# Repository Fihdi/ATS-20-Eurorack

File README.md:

# 10hp Radio Module

An ATS-20 Radio port in 3U height. Jumpers on the PCB lets the device be used as an Eurorack module or as a standalone all-band receiver.

A regular 12V DC adapter or a 9V battery can be used for standalone usage.

# Jumpers

Changing the jumper on the back of the module from **SA** (Stand Alone mode) to **ER** (Eurorack mode) changes the output from headphone level to Eurorack level. In stand alone mode, the radio output is routed to an LM386 class AB amplifier. An 8-Ohm speaker can be connected to the amplifier with the **SP+** and **SP-** screw terminals.

The I2C ADDR jumpers change the I2C address of the SI4732 IC.

# 3D Model

The 3D model for the case was designed by [SapuSeven](https://github.com/SapuSeven). The model in this github project is designed for the AS03208AS-HT speaker by PUI audio. The .step model can be downloaded and modified to fit different speakers.

# Sponsorship

The module that you see in the picture above is using circuit boards that were fabricated by [PCBWay](https://www.pcbway.com/) They have excellent build quality and I can recommend using their service to build your own projects! I used the "Black" option for the soldermask and the surface has very deep and glossy black finish, which looks amazing, they also have an option for a "Matte Black" finish which I will try next time. Thank you PCBWay for sponsoring this module. 
This is the first project that features a small OLED display, and thus the first project where I cut out a square section from the frontplate. This worked out really well and the corners are clean 90 degrees with no rounding. They are also having a 3D printing service, which means you can order the boards and the case for this radio all in one place.

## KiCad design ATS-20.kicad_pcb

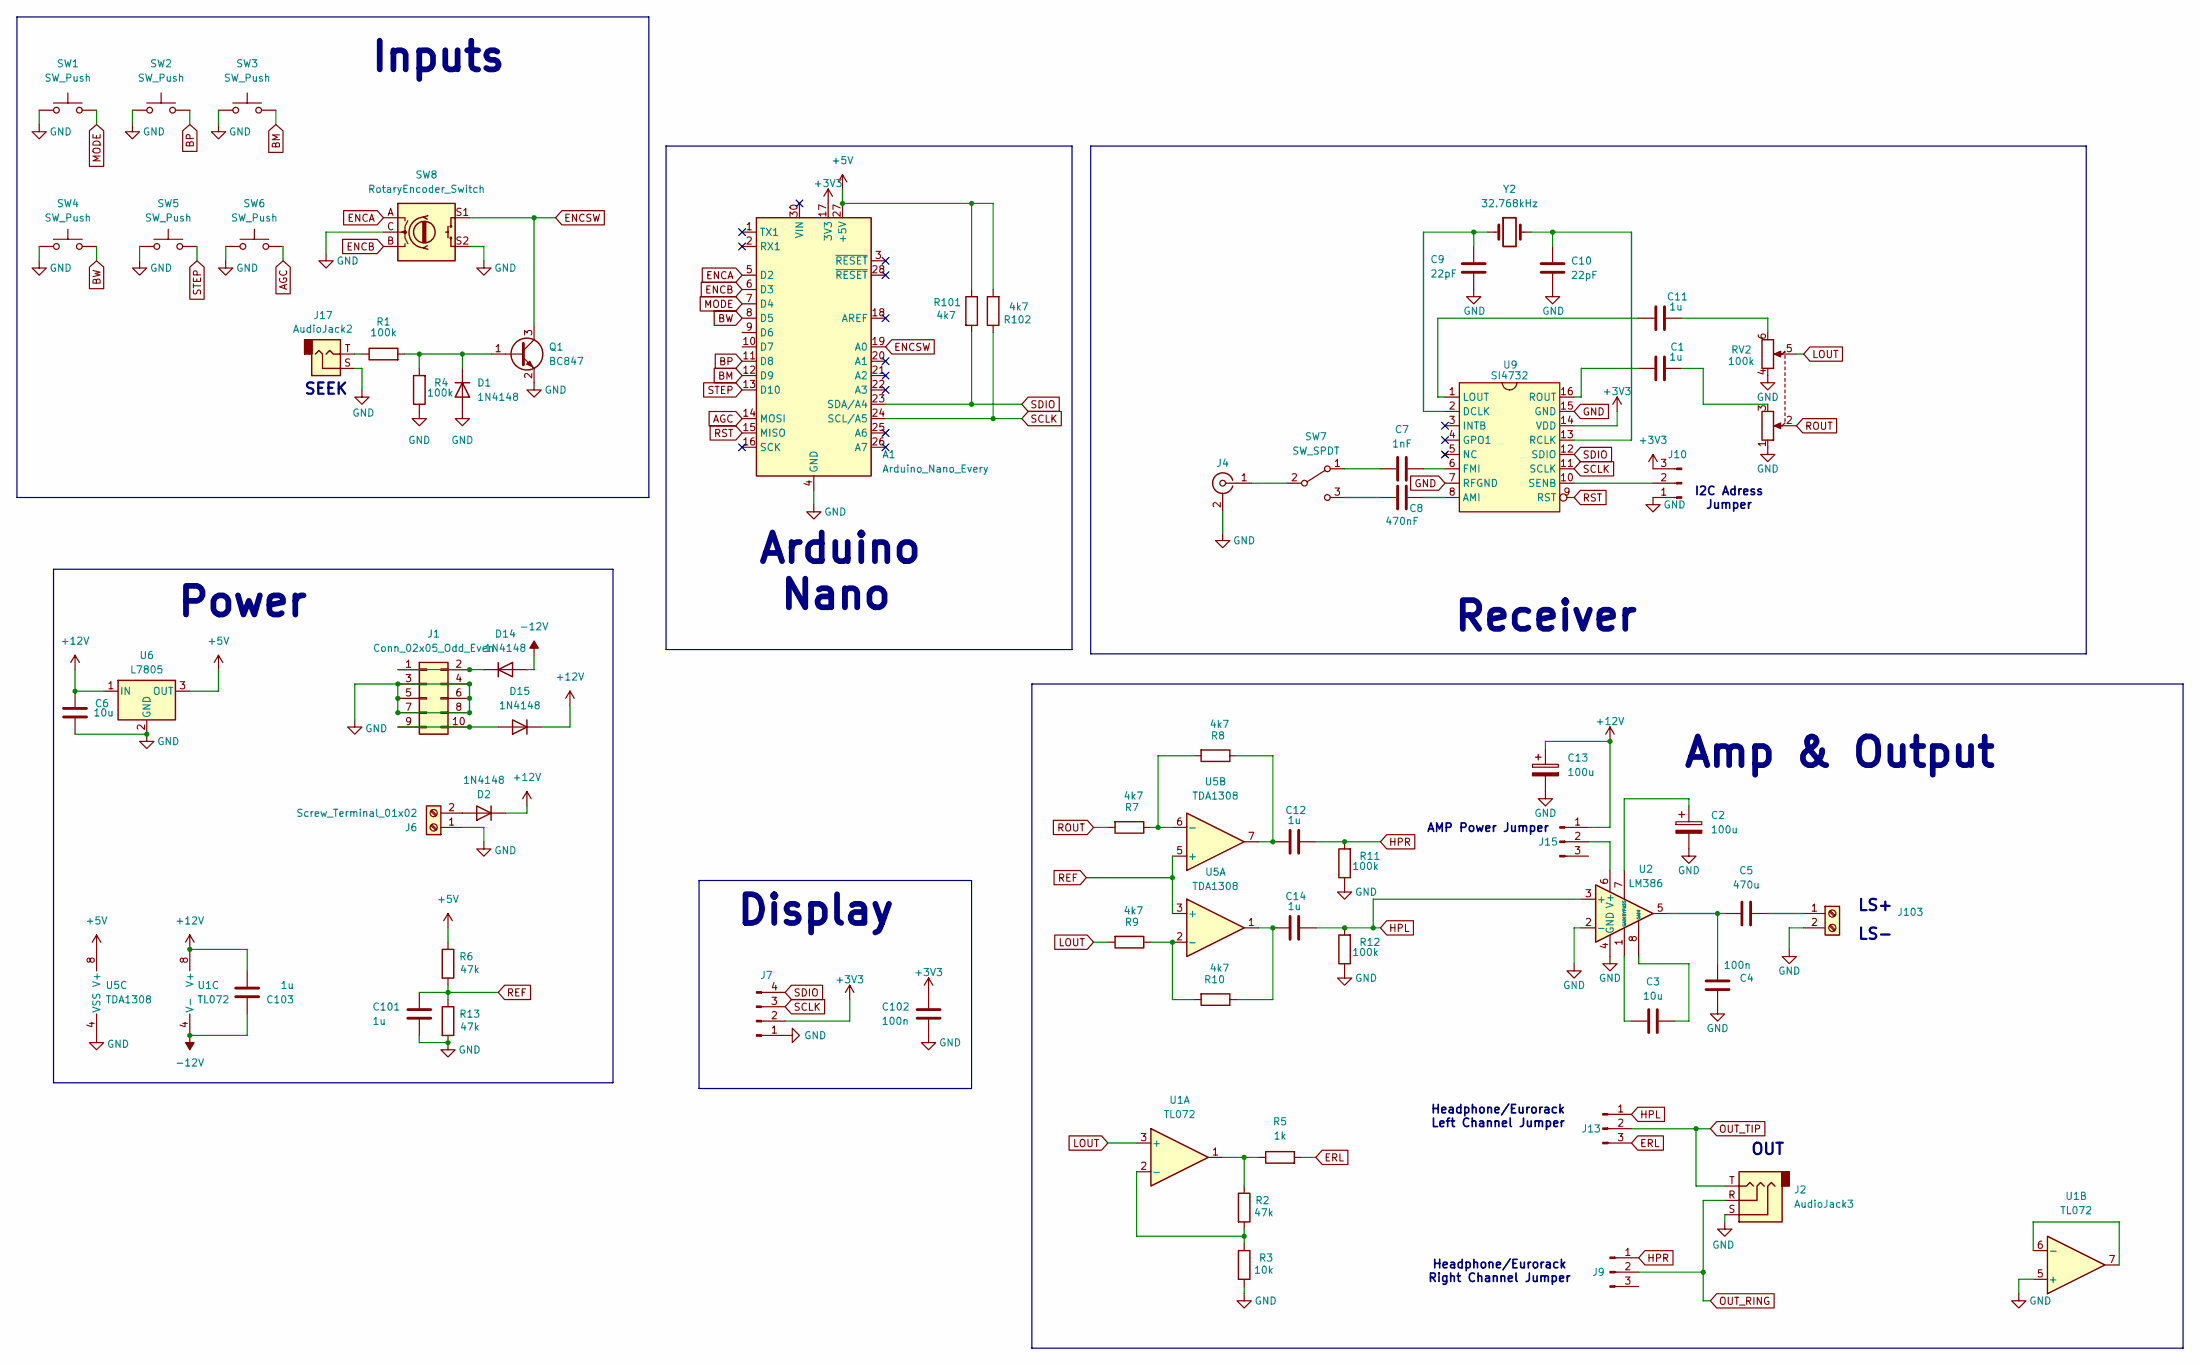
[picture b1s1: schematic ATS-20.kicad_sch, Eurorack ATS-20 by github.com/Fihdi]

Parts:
A1: Arduino_Nano_Every; Arduino_Nano
C1, C11, C12, C14, C101, C103: 1u; C_0805_2012Metric
C2, C13: 100u; C_Elec_6.3x7.7
C3, C6: 10u; C_0805_2012Metric
C4, C102: 100n; C_0805_2012Metric
C5: 470u; C_Elec_6.3x7.7
C7: 1nF; C_0805_2012Metric
C8: 470nF; C_0805_2012Metric
C9, C10: 22pF; C_0805_2012Metric
D1, D2, D14, D15: 1N4148; D_SOD-323_HandSoldering
J1: Conn_02x05_Odd_Even; IDC-Header_2x05_P2.54mm_Vertical
J2: AudioJack3; StereoTRS
J4: Conn_Coaxial; BNC5-J-P-GN-ST-TH2D
J6: Screw_Terminal_01x02; TerminalBlock_Phoenix_MKDS-1,5-2-5.08_1x02_P5.08mm_Horizont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
J7: Conn_01x04_Pin; PinSocket_1x04_P2.54mm_Vertical
J9, J10, J13, J15: Conn_01x02_Pin; PinHeader_1x03_P2.54mm_Vertical
J17: AudioJack2; MonoTRS
J103: Screw_Terminal_01x02; TerminalBlock_RND_205-00287_1x02_P5.08mm_Horizontal
Q1: BC847; SOT-23
R1, R4, R11, R12: 100k; R_0805_2012Metric
R2, R6, R13: 47k; R_0805_2012Metric
R3: 10k; R_0805_2012Metric
R5: 1k; R_0805_2012Metric
R7, R8, R9, R10, R101, R102: 4k7; R_0805_2012Metric
RV2: 100k; Potentiometer_Alpha_RD902F-40-00D_Dual_Vertical
SW1, SW2, SW3, SW4, SW5, SW6: SW_Push; PushButton
SW7: SW_SPDT; Switch
SW8: RotaryEncoder_Switch; RotaryEncoder_Alps_EC11E-Switch_Vertical_H20mm
U1: TL072; SOIC-8_3.9x4.9mm_P1.27mm
U2: LM386; SOIC-8_3.9x4.9mm_P1.27mm
U5: TDA1308; SOIC-8_3.9x4.9mm_P1.27mm
U6: L7805; SOT-223-3_TabPin2
U9: SI4732; SOIC-16_4.55x10.3mm_P1.27mm
Y2: 32.768kHz; Crystal_Round_D3.0mm_Vertical

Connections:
+3V3: A1.17 (3V3), C102.2, J7.2, J10.3, U9.14 (VDD)
+5V: A1.27 (+5V), R6.1, R101.1, R102.2, U5.8 (V+), U6.3 (OUT)
+12V: C6.1, C13.1, C103.1, D2.1 (K), D15.1 (K), J15.1, U1.8 (V+), U6.1 (IN)
-12V: C103.2, D14.2 (A), U1.4 (V-)
AGC: A1.14 (MOSI), SW6.2
BM: A1.12 (D9), SW3.2
BP: A1.11 (D8), SW2.2
BW: A1.8 (D5), SW4.2
ENCA: A1.5 (D2), SW8.A
ENCB: A1.6 (D3), SW8.B
ENCSW: A1.19 (A0), Q1.3 (C), SW8.S1
ERL: J13.3, R5.2
GND: A1.4 (GND), A1.29 (GND), C2.2, C4.1, C6.2, C9.2, C10.2, C13.2, C101.1, C102.1, D1.2 (A), J1.3, J1.4, J1.5, J1.6, J1.7, J1.8, J2.S, J4.2 (Ext), J6.1, J7.1, J10.1, J17.S, J103.2, Q1.2 (E), R3.2, R4.1, R11.1, R12.1, R13.2, RV2.1, RV2.4, SW1.1, SW2.1, SW3.1, SW4.1, SW5.1, SW6.1, SW8.C, SW8.S2, U1.5 (+), U2.2 (-), U2.4 (GND), U5.4 (VSS), U6.2 (GND), U9.7 (RFGND), U9.15 (GND)
HPL: C14.2, J13.1, R12.2, U2.3 (+)
HPR: C12.2, J9.1, R11.2
LOUT: R9.2, RV2.5, U1.3 (+)
MODE: A1.7 (D4), SW1.2
unnamed: C1.2, RV2.3
unnamed: C3.1, U2.8 (GAIN)
unnamed: C3.2, U2.1 (GAIN)
unnamed: C4.2, C5.2, U2.5
unnamed: C11.2, RV2.6
unnamed: C12.1, R8.1, U5.7
unnamed: C14.1, R10.1, U5.1
unnamed: D1.1 (K), Q1.1 (B), R1.2, R4.2
unnamed: D2.2 (A), J6.2
unnamed: D14.1 (K), J1.1, J1.2
unnamed: D15.2 (A), J1.9, J1.10
unnamed: J4.1 (In), SW7.2 (B)
unnamed: J10.2, U9.10 (SENB)
unnamed: J15.2, U2.6 (V+)
unnamed: J17.T, R1.1
unnamed: C5.1, J103.1
unnamed: R2.1, R5.1, U1.1
unnamed: C7.2, SW7.1 (A)
unnamed: C8.2, SW7.3 (C)
unnamed: R2.2, R3.1, U1.2 (-)
unnamed: U1.6 (-), U1.7
unnamed: C2.1, U2.7 (BYPASS)
unnamed: R9.1, R10.2, U5.2 (-)
unnamed: R7.1, R8.2, U5.6 (-)
unnamed: C8.1, U9.8 (AMI)
unnamed: C9.1, U9.2 (DCLK), Y2.1
unnamed: C7.1, U9.6 (FMI)
unnamed: C11.1, U9.1 (LOUT)
unnamed: C10.1, U9.13 (RCLK), Y2.2
unnamed: C1.1, U9.16 (ROUT)
OUT_RING: J2.R, J9.2
OUT_TIP: J2.T, J13.2
REF: C101.2, R6.2, R13.1, U5.3 (+), U5.5 (+)
ROUT: R7.2, RV2.2
RST: A1.15 (MISO), U9.9 (RST)
SCLK: A1.24 (SCL/A5), J7.3, R102.1, U9.11 (SCLK)
SDIO: A1.23 (SDA/A4), J7.4, R101.2, U9.12 (SDIO)
STEP: A1.13 (D10), SW5.2

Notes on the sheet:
SEEK
Power
OUT
Display
I2C Adress Jumper
Amp & Output
Headphone/Eurorack Left Channel Jumper
Headphone/Eurorack Right Channel Jumper
Arduino Nano
LS-
Inputs
Receiver
LS+
AMP Power Jumper

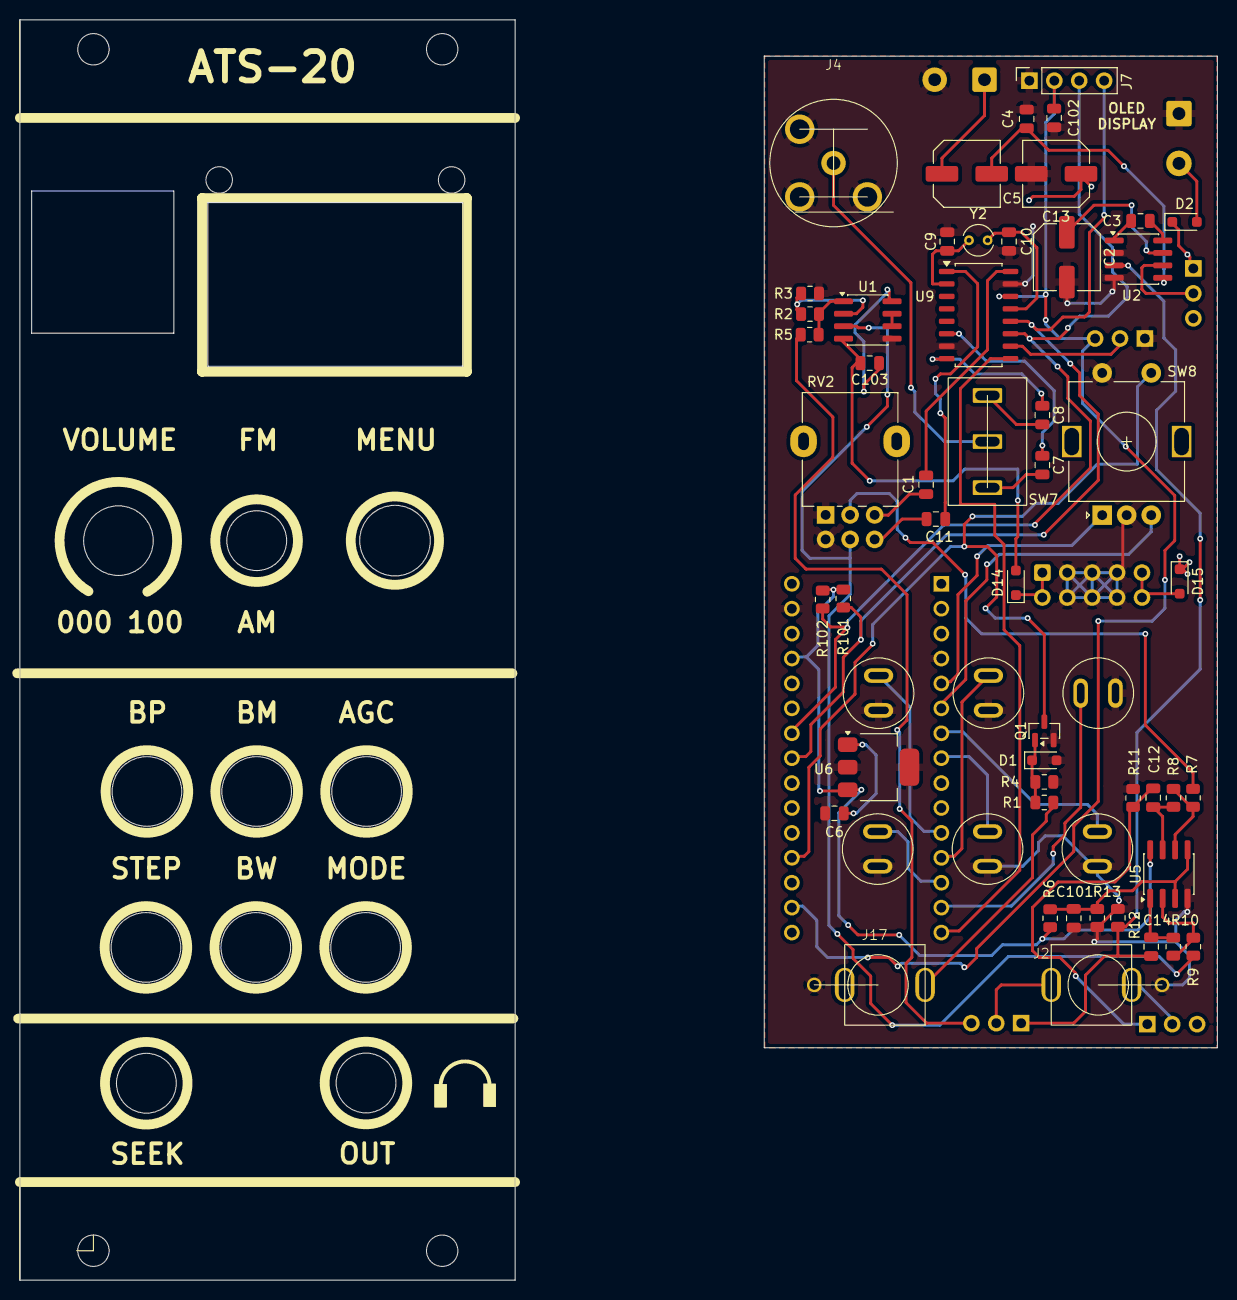
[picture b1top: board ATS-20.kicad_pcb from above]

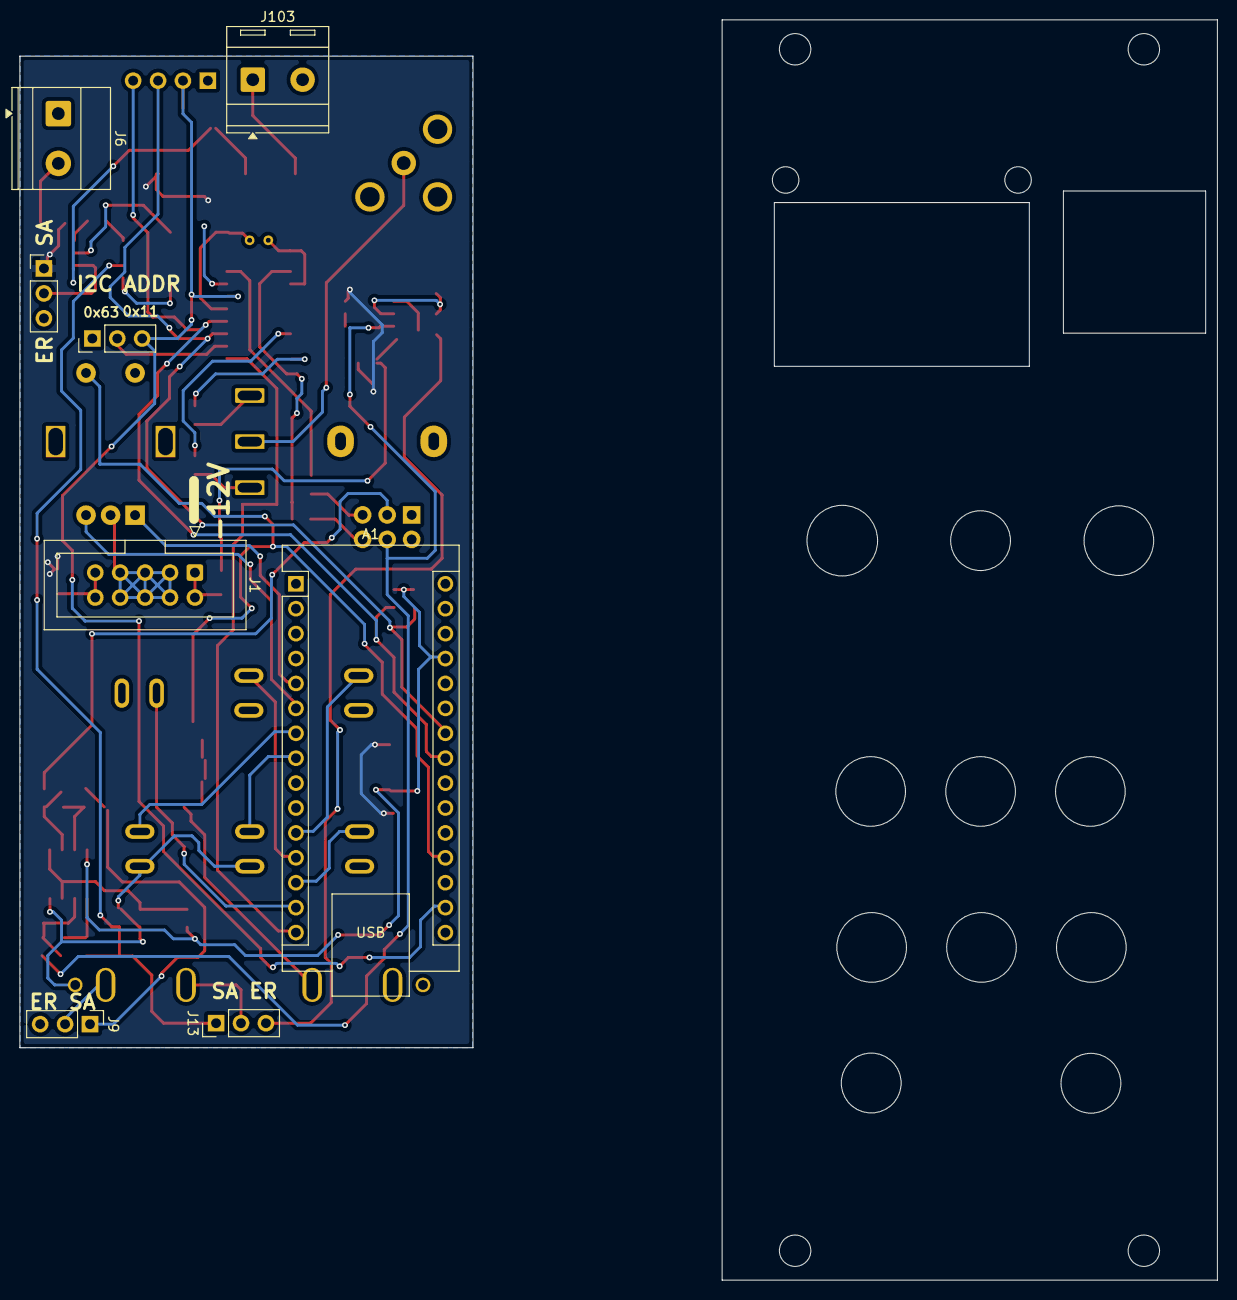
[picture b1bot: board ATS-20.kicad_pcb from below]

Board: 2 copper layers, 46.2 x 101.1 mm, 64 parts (8 on the bottom side), 55 nets.

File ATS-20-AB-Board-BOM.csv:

Reference,Qty,Value,Footprint,Datasheet
A1,1,Arduino_Nano_Every,Module:Arduino_Nano,https://content.arduino.cc/assets/NANOEveryV3.0_sch.pdf
"C1,C11,C12,C14,C101,C103",6,1u,Capacitor_SMD:C_0805_2012Metric,
"C2,C13",2,100u,Capacitor_SMD:C_Elec_6.3x7.7,
"C3,C6",2,10u,Capacitor_SMD:C_0805_2012Metric,
"C4,C102",2,100n,Capacitor_SMD:C_0805_2012Metric,
C5,1,470u,Capacitor_SMD:C_Elec_6.3x7.7,
C7,1,1nF,Capacitor_SMD:C_0805_2012Metric,
C8,1,470nF,Capacitor_SMD:C_0805_2012Metric,
"C9,C10",2,22pF,Capacitor_SMD:C_0805_2012Metric,
"D1,D2,D14,D15",4,1N4148,Diode_SMD:D_SOD-323_HandSoldering,
J1,1,Conn_02x05_Odd_Even,Connector_IDC:IDC-Header_2x05_P2.54mm_Vertical,
J2,1,AudioJack3,Library:StereoTRS,
J4,1,Conn_Coaxial,Library:BNC5-J-P-GN-ST-TH2D,
J6,1,Screw_Terminal_01x02,"TerminalBlock_Phoenix:TerminalBlock_Phoenix_MKDS-1,5-2-5.08_1x02_P5.08mm_Horizontal",
J7,1,Conn_01x04_Pin,Connector_PinSocket_2.54mm:PinSocket_1x04_P2.54mm_Vertical,
"J9,J10,J13,J15",4,Conn_01x02_Pin,Connector_PinHeader_2.54mm:PinHeader_1x03_P2.54mm_Vertical,
J17,1,AudioJack2,Library:MonoTRS,
J103,1,Screw_Terminal_01x02,TerminalBlock_RND:TerminalBlock_RND_205-00287_1x02_P5.08mm_Horizontal,
Q1,1,BC847,Package_TO_SOT_SMD:SOT-23,http://www.infineon.com/dgdl/Infineon-BC847SERIES_BC848SERIE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
"R1,R4,R11,R12",4,100k,Resistor_SMD:R_0805_2012Metric,
"R2,R6,R13",3,47k,Resistor_SMD:R_0805_2012Metric,
R3,1,10k,Resistor_SMD:R_0805_2012Metric,
R5,1,1k,Resistor_SMD:R_0805_2012Metric,
"R7,R8,R9,R10,R101,R102",6,4k7,Resistor_SMD:R_0805_2012Metric,
RV2,1,100k,Potentiometer_THT:Potentiometer_Alpha_RD902F-40-00D_Dual_Vertical,
"SW1,SW2,SW3,SW4,SW5,SW6",6,SW_Push,Library:PushButton,
SW7,1,SW_SPDT,Library:Switch,
SW8,1,RotaryEncoder_Switch,Rotary_Encoder:RotaryEncoder_Alps_EC11E-Switch_Vertical_H20mm,
U1,1,TL072,Package_SO:SOIC-8_3.9x4.9mm_P1.27mm,http://www.ti.com/lit/ds/symlink/tl071.pdf
U2,1,LM386,Package_SO:SOIC-8_3.9x4.9mm_P1.27mm,http://www.ti.com/lit/ds/symlink/lm386.pdf
U5,1,TDA1308,Package_SO:SOIC-8_3.9x4.9mm_P1.27mm,https://www.nxp.com/docs/en/data-sheet/TDA1308.pdf
U6,1,L7805,Package_TO_SOT_SMD:SOT-223-3_TabPin2,http://www.st.com/content/ccc/resource/technical/document/da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
U9,1,SI4732,Package_SO:SOIC-16_4.55x10.3mm_P1.27mm,
Y2,1,32.768k,Crystal:Crystal_Round_D3.0mm_Vertical,

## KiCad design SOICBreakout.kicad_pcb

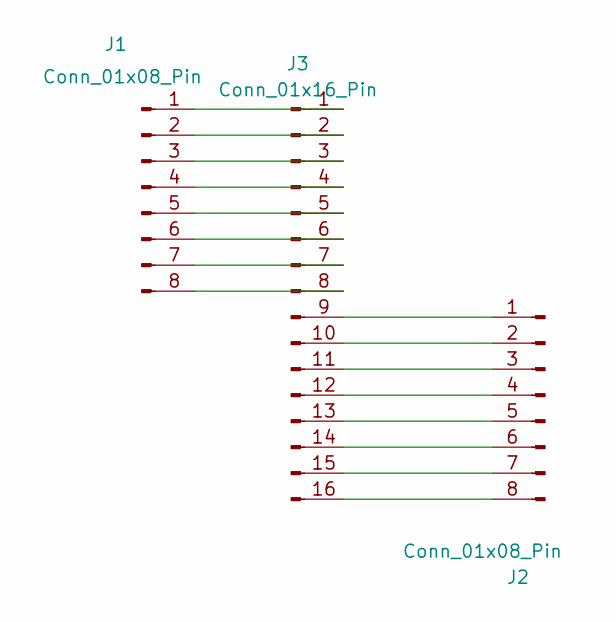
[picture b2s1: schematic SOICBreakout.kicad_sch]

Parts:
J1, J2: Conn_01x08_Pin; PinHeader_1x08_P2.54mm_Vertical
J3: Conn_01x16_Pin; SOIC-16_4.55x10.3mm_P1.27mm

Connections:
unnamed: J1.1, J3.1
unnamed: J1.2, J3.2
unnamed: J1.3, J3.3
unnamed: J1.4, J3.4
unnamed: J1.5, J3.5
unnamed: J1.6, J3.6
unnamed: J1.7, J3.7
unnamed: J1.8, J3.8
unnamed: J2.1, J3.9
unnamed: J2.2, J3.10
unnamed: J2.3, J3.11
unnamed: J2.4, J3.12
unnamed: J2.5, J3.13
unnamed: J2.6, J3.14
unnamed: J2.7, J3.15
unnamed: J2.8, J3.16

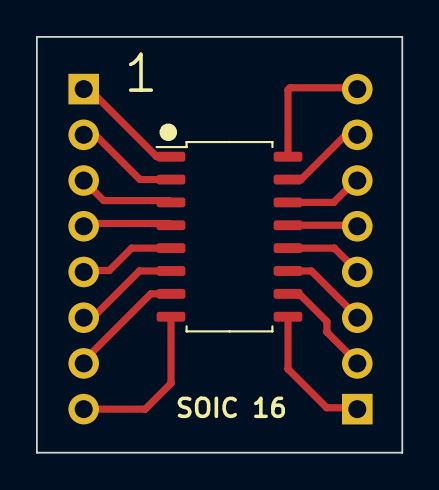
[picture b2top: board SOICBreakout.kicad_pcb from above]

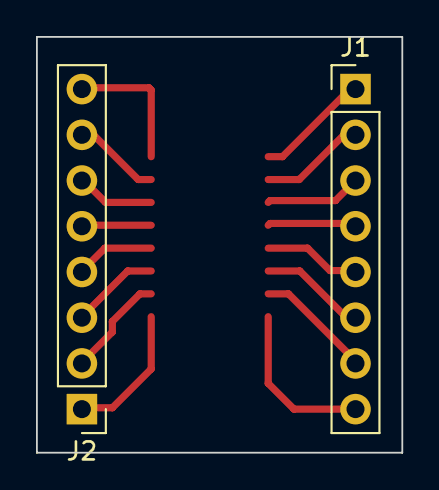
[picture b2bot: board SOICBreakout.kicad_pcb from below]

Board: 2 copper layers, 20.3 x 23.1 mm, 3 parts (2 on the bottom side), 16 nets.

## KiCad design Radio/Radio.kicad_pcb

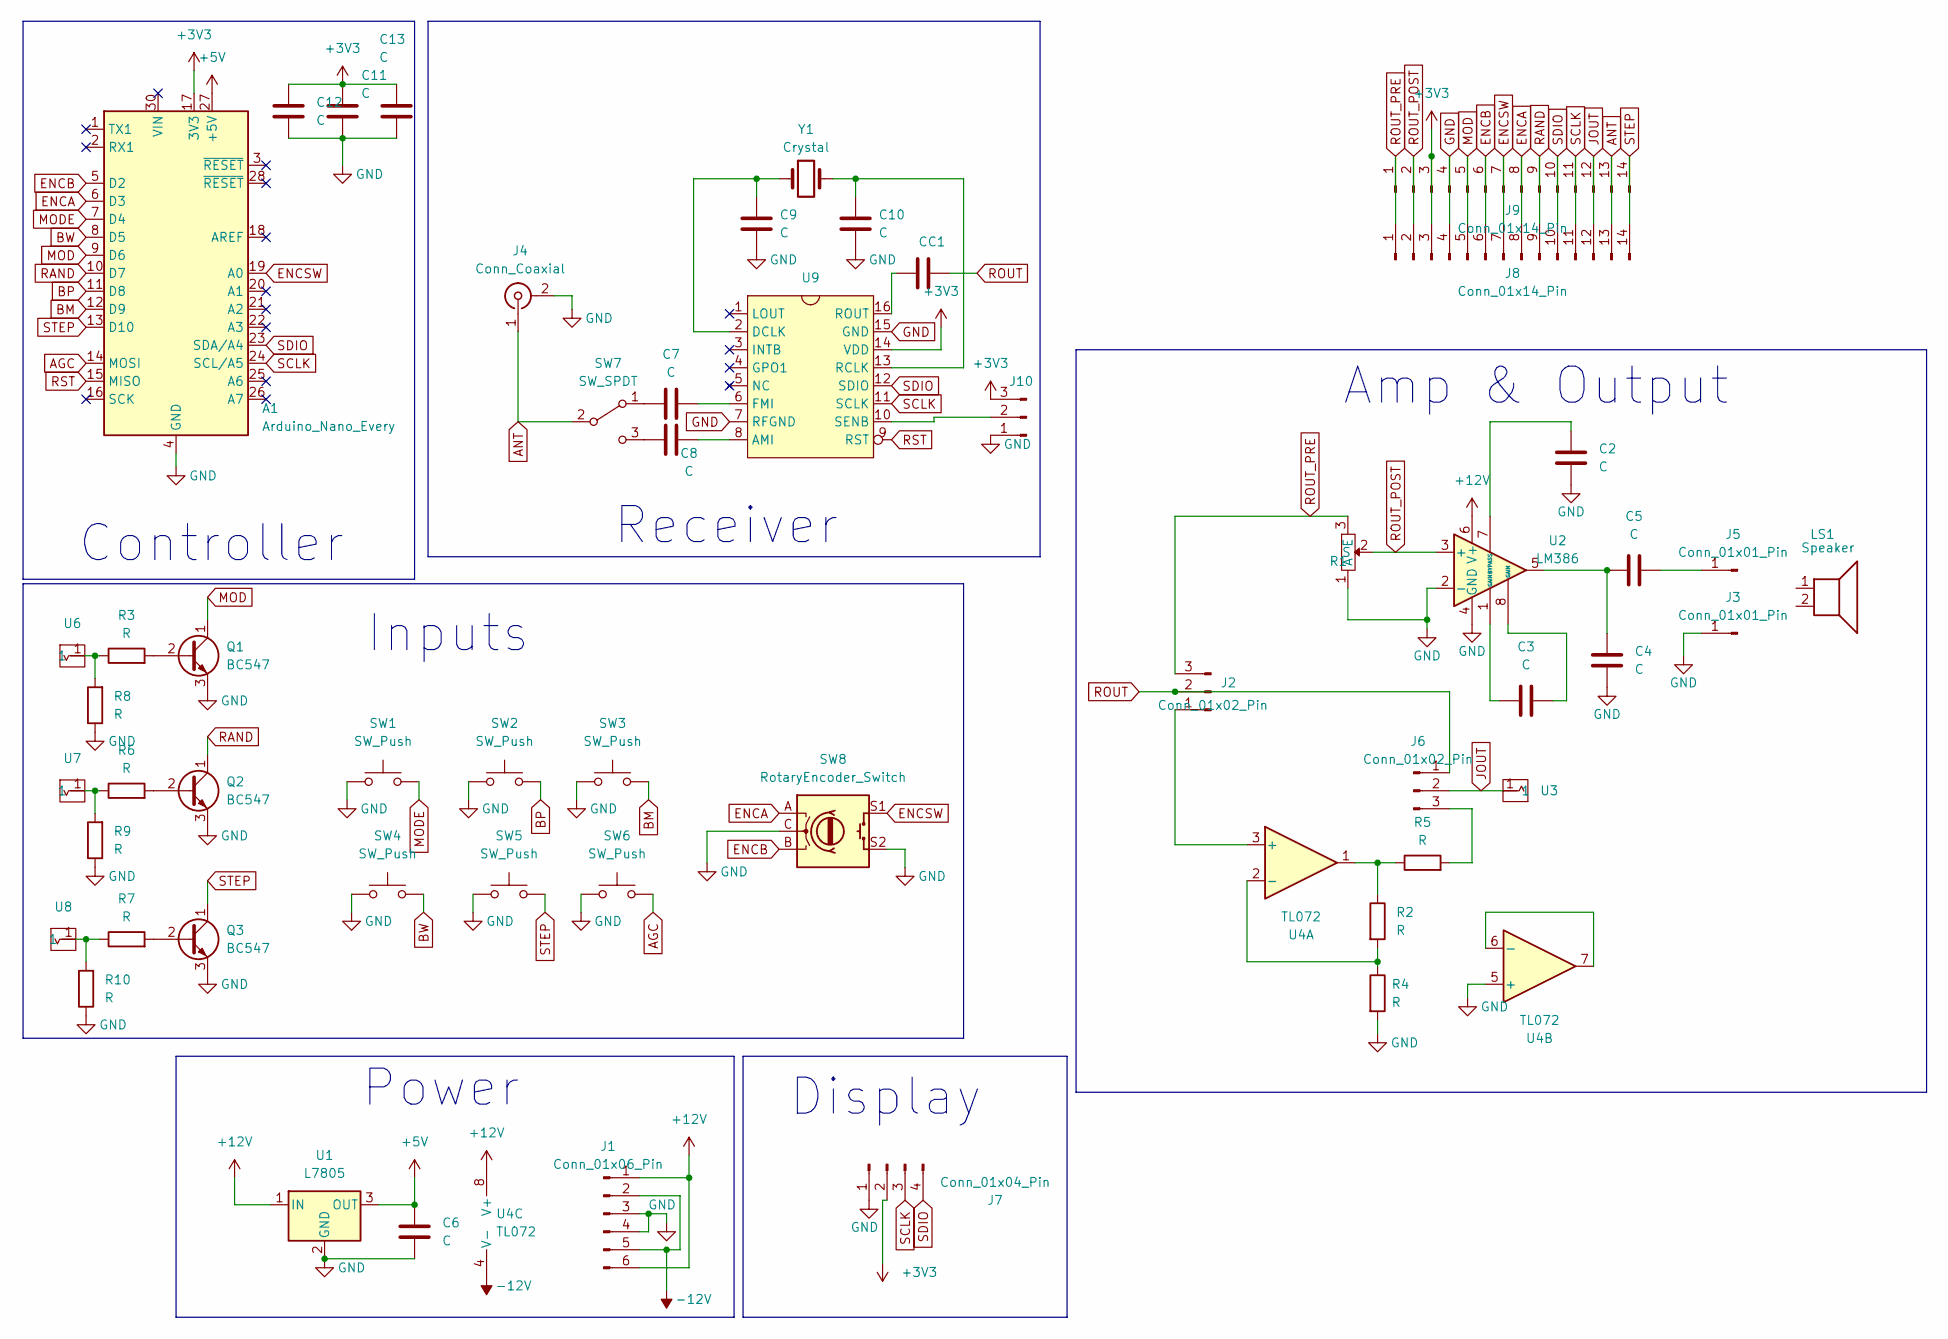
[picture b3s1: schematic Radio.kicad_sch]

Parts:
A1: Arduino_Nano_Every; Arduino_Nano
C1, C2, C3, C4, C5, C6, C7, C8, C9, C10, C11, C12: C; C_Rect_L9.0mm_W2.5mm_P7.50mm_MKT
C13: C; C_Rect_L7.2mm_W2.5mm_P5.00mm_FKS2_FKP2_MKS2_MKP2
J1: Conn_01x06_Pin; PinHeader_1x06_P2.54mm_Vertical
J2, J6, J10: Conn_01x02_Pin; PinHeader_1x03_P2.54mm_Vertical
J3, J5: Conn_01x01_Pin; PinSocket_1x01_P2.54mm_Vertical
J4: Conn_Coaxial; BNC_TEConnectivity_1478035_Horizontal
J7: Conn_01x04_Pin; PinSocket_1x04_P2.54mm_Vertical
J8: Conn_01x14_Pin; PinHeader_1x14_P2.54mm_Vertical
J9: Conn_01x14_Pin; PinSocket_1x14_P2.54mm_Vertical
LS1: Speaker
Q1, Q2, Q3: BC547; TO-92_Inline_Wide
R1: AlpsPot
R2, R3, R4, R5, R6, R7, R8, R9, R10: R; R_Axial_DIN0204_L3.6mm_D1.6mm_P7.62mm_Horizontal
SW1, SW2, SW3, SW4, SW5, SW6: SW_Push; PinSocket_1x02_P2.54mm_Vertical
SW7: SW_SPDT; PinHeader_1x03_P2.54mm_Vertical
SW8: RotaryEncoder_Switch; RotaryEncoder_Alps_EC11E-Switch_Vertical_H20mm
U1: L7805; TO-220-3_Vertical
U2: LM386; DIP-8_W7.62mm
U3, U6, U7, U8: Aux_flush; aux_flush
U4: TL072; DIP-8_W7.62mm
U9: SOIC-16_4.55x10.3mm_P1.27mm
Y1: Crystal; Crystal_DS26_D2.0mm_L6.0mm_Vertical

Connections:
+3V3: A1.17 (3V3), C11.1, C12.1, C13.1, J7.2, J8.3, J9.3, J10.3, U9.14 (VDD)
+5V: A1.27 (+5V), C6.1, U1.3 (OUT)
+12V: J1.1, J1.6, U1.1 (IN), U2.6 (V+), U4.8 (V+)
-12V: J1.2, J1.5, U4.4 (V-)
AGC: A1.14 (MOSI), SW6.2
ANT: J4.1 (In), J8.13, J9.13, SW7.2 (B)
BM: A1.12 (D9), SW3.2
BP: A1.11 (D8), SW2.2
BW: A1.8 (D5), SW4.2
ENCA: A1.6 (D3), J8.8, J9.8, SW8.A
ENCB: A1.5 (D2), J8.6, J9.6, SW8.B
ENCSW: A1.19 (A0), J8.7, J9.7, SW8.S1
GND: A1.4 (GND), A1.29 (GND), C2.1, C4.1, C6.2, C9.2, C10.2, C11.2, C12.2, C13.2, J1.3, J1.4, J3.1, J4.2 (Ext), J7.1, J8.4, J9.4, J10.1, Q1.3 (E), Q2.3 (E), Q3.3 (E), R1.1 (A), R4.2, R8.1, R9.1, R10.1, SW1.1, SW2.1, SW3.1, SW4.1, SW5.1, SW6.1, SW8.C, SW8.S2, U1.2 (GND), U2.2 (-), U2.4 (GND), U4.5 (+), U9.7 (RFGND), U9.15 (GND)
JOUT: J6.2, J8.12, J9.12, U3.1
MOD: A1.9 (D6), J8.5, J9.5, Q1.1 (C)
MODE: A1.7 (D4), SW1.2
unnamed: C3.1, U2.8 (GAIN)
unnamed: C3.2, U2.1 (GAIN)
unnamed: C4.2, C5.2, U2.5
unnamed: J2.1, U4.3 (+)
unnamed: C5.1, J5.1
unnamed: J6.3, R5.2
unnamed: J10.2, U9.10 (SENB)
unnamed: Q1.2 (B), R3.2
unnamed: Q2.2 (B), R6.2
unnamed: Q3.2 (B), R7.2
unnamed: R2.1, R5.1, U4.1
unnamed: R3.1, R8.2, U6.1
unnamed: R6.1, R9.2, U7.1
unnamed: R7.1, R10.2, U8.1
unnamed: C7.2, SW7.1 (A)
unnamed: C8.2, SW7.3 (C)
unnamed: C2.2, U2.7 (BYPASS)
unnamed: R2.2, R4.1, U4.2 (-)
unnamed: U4.6 (-), U4.7
unnamed: C8.1, U9.8 (AMI)
unnamed: C9.1, U9.2 (DCLK), Y1.1
unnamed: C7.1, U9.6 (FMI)
unnamed: C10.1, U9.13 (RCLK), Y1.2
unnamed: C1.1, U9.16 (ROUT)
RAND: A1.10 (D7), J8.9, J9.9, Q2.1 (C)
ROUT: C1.2, J2.2, J6.1
ROUT_POST: J8.2, J9.2, R1.2 (S), U2.3 (+)
ROUT_PRE: J2.3, J8.1, J9.1, R1.3 (E)
RST: A1.15 (MISO), U9.9 (RST)
SCLK: A1.24 (SCL/A5), J7.3, J8.11, J9.11, U9.11 (SCLK)
SDIO: A1.23 (SDA/A4), J7.4, J8.10, J9.10, U9.12 (SDIO)
STEP: A1.13 (D10), J8.14, J9.14, Q3.1 (C), SW5.2

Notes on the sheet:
Amp & Output
Controller
Power
Display
Inputs
Receiver

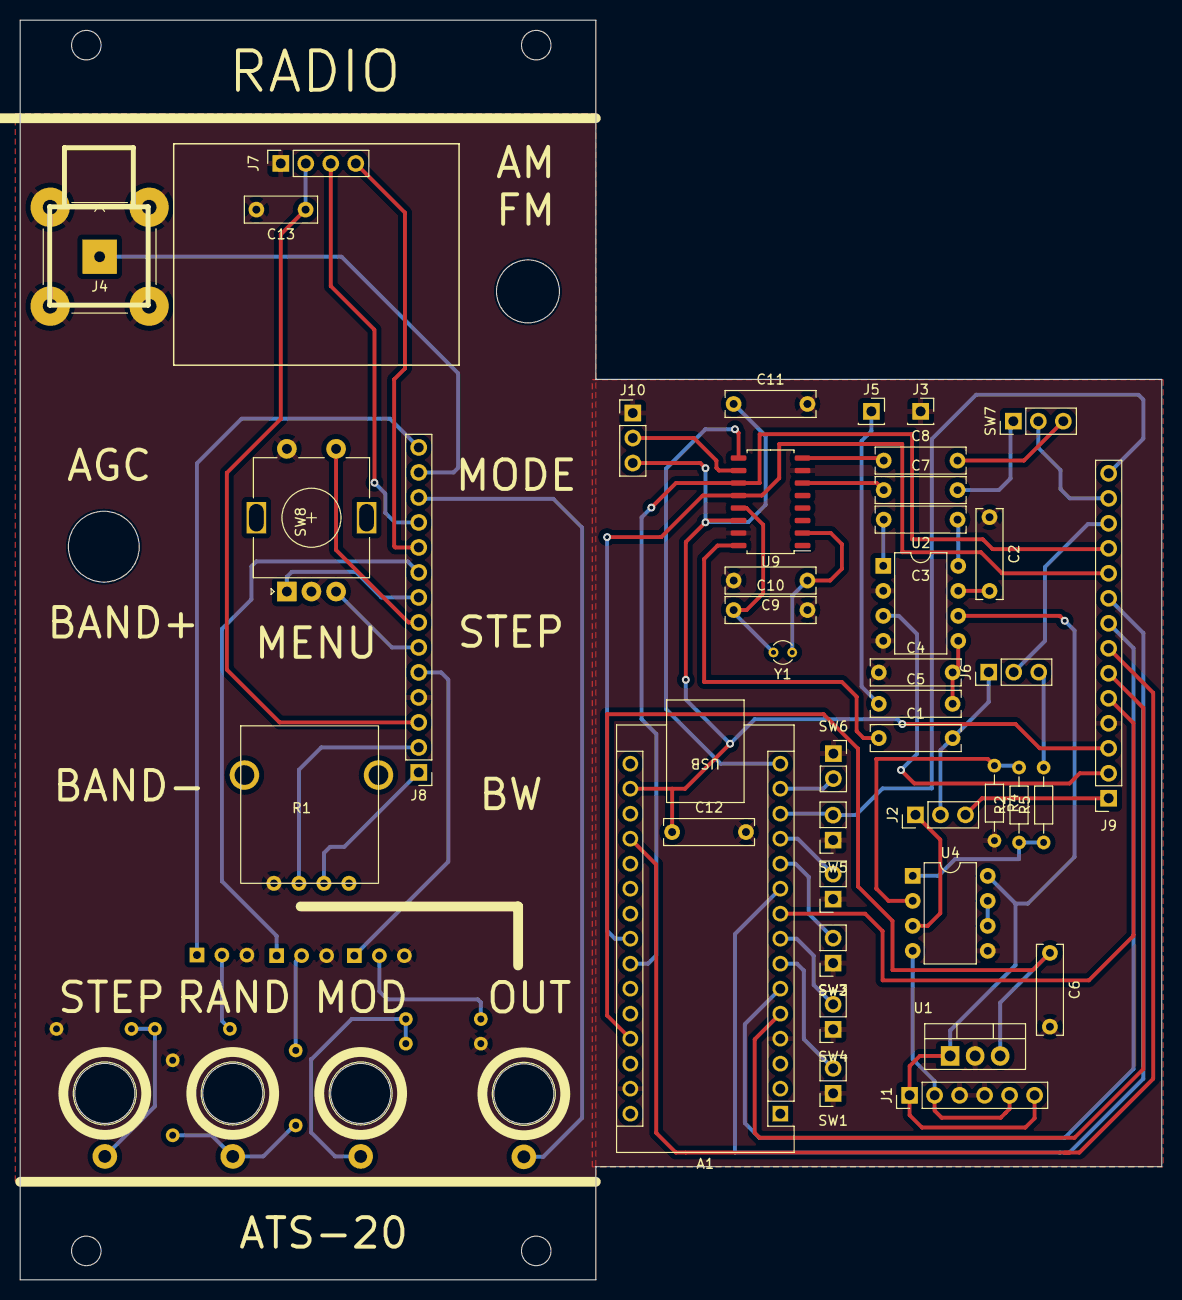
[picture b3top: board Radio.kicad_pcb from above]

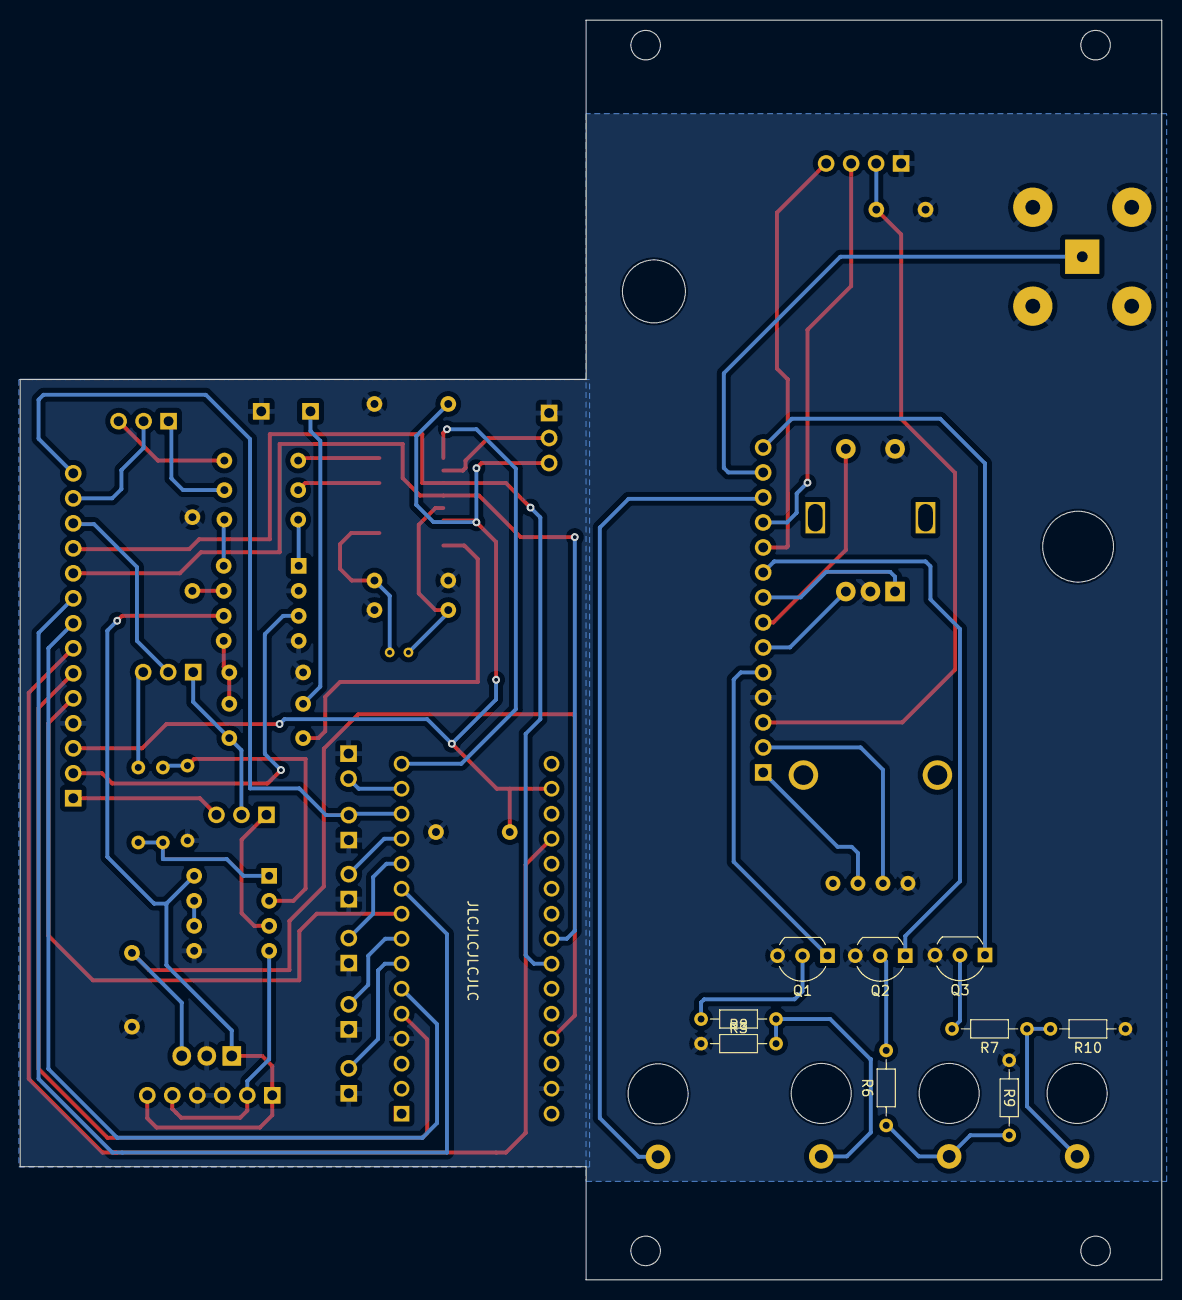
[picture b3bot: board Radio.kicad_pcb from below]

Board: 2 copper layers, 116.0 x 128.0 mm, 54 parts (9 on the bottom side), 48 nets.
